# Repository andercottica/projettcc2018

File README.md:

# projettcc2018
Trabalho Conclusão de Curso Engenharia Eletrônica
Alunos: Anderson Cottica e Victor Hugo Laynez

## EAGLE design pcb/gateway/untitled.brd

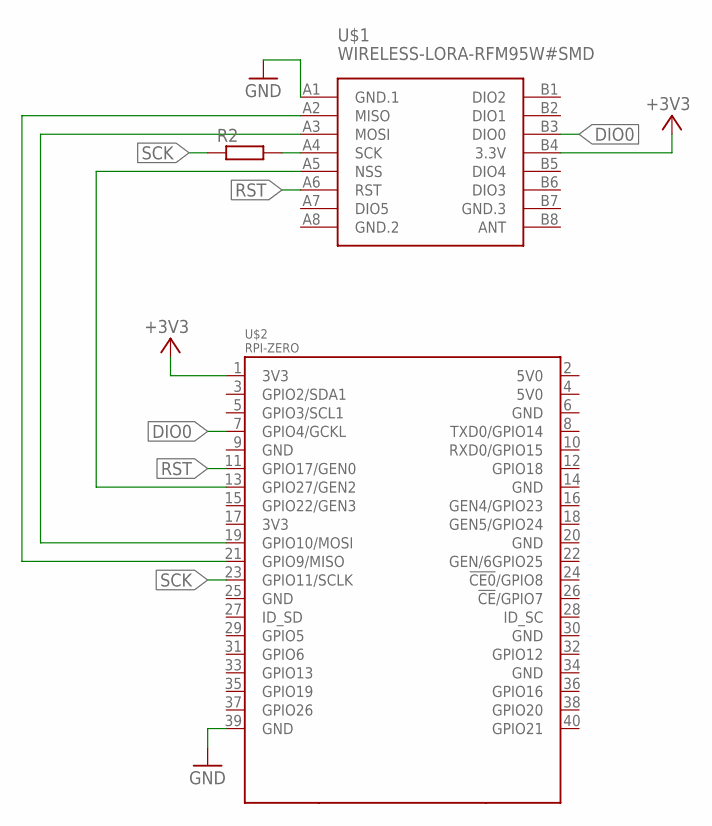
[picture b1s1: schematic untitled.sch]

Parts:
R2: R-EU_0204/5; 0204/5
U$1: WIRELESS-LORA-RFM95W#SMD
U$2: RPI-ZERO; RASPBERRYPI_BASTELSTUBE_V13_RASPI_BOARD_B+_FULL

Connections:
+3V3: U$1.B4 (3.3V), U$2.1 (3V3)
DIO0: U$1.B3 (DIO0), U$2.7 (GPIO4/GCKL)
GND: U$1.A1 (GND.1), U$2.39 (GND)
GND.2: U$1.A8 (GND.2)
GND.3: U$1.B7 (GND.3)
unnamed: U$1.A3 (MOSI), U$2.19 (GPIO10/MOSI)
unnamed: R2.2, U$1.A4 (SCK)
unnamed: U$1.A5 (NSS), U$2.13 (GPIO27/GEN2)
unnamed: U$1.A2 (MISO), U$2.21 (GPIO9/MISO)
RST: U$1.A6 (RST), U$2.11 (GPIO17/GEN0)
SCK: R2.1, U$2.23 (GPIO11/SCLK)

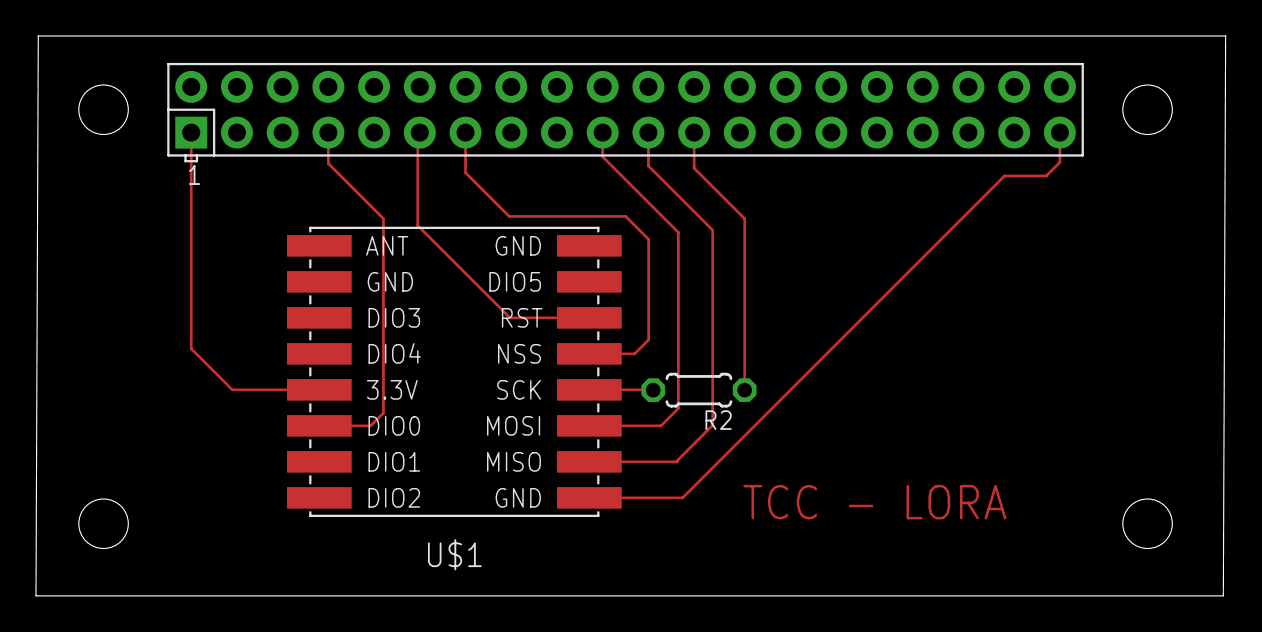
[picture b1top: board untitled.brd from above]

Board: 2 copper layers, 66.1 x 31.1 mm, 3 parts (0 on the bottom side), 9 nets.

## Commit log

2018-12-16 Código usado para o endpoint lora
2019-01-13 Arquivos iniciais web app
2019-01-18 atualizado gitignore
2019-01-18 atualizado codigo do webapp
2019-01-18 no message
2019-02-10 teste com graficos na home page
2019-02-20 gráfico adicionado
2019-02-22 Adicionado comparação de medidas
2019-02-27 Adicionado media brasil ao grafico
2019-02-27 corrigido ponto por virgula
2019-03-03 corrigido data do dia de consulta
2019-03-23 Add files via upload
    Código do hidrometro
2019-03-25 Arquivo no padrão de endnode
2019-04-01 conta de agua
2019-04-02 melhoria conta de agua
2019-04-03 Pagina de conta de agua e esgoto concluída.
2019-04-03 Adicionado limite de 10 linhas no histórico
2019-04-20 Gráfico alterado para média da ONU conforme trabalho escrito
2019-05-05 pcb shield gateway
2019-05-05 codigo do hidrometro para bluepill
2019-05-05 sensor fluxo para bluepill
2019-05-05 código funcionando no blue pill
2019-05-11 corrigido dias da semana do grafico e conta;
2019-07-03 grafico pegando ultimos 7 dias

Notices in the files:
parts and their libraries:
diy-modules: Released under the Creative Commons Attribution 4.0 International License: http://creativecommons.org/licenses/by/4.0
